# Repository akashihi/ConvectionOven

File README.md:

<!-- Improved compatibility of back to top link: See: https://github.com/othneildrew/Best-README-Template/pull/73 -->

<h3 align="center">Adler Ad 6304 Convection Oven controller board</h3>
<div>
  <p align="center">
    Modern replacement for the Adler Ad 6304 control circuit. 
    <br />
    <a href="https://github.com/akashihi/ConvectionOven"><strong>Explore the docs »</strong></a>
    <br />
    <br />
  </p>
</div>

<!-- TABLE OF CONTENTS -->
<details>
  <summary>Table of Contents</summary>
  <ol>
    <li>
      <a href="#about-the-project">About The Project</a>
    </li>
    <li>
      <a href="#getting-started">Getting Started</a>
      <ul>
        <li><a href="#housing">Housing</a></li>
        <li><a href="#controls">Controls</a></li>
        <li><a href="#hall-sensor">Hall sensor</a></li>
        <li><a href="#pcb">PCB</a></li>
        <li><a href="#firmware">Firmware</a></li>
      </ul>
    </li>
    <li><a href="#usage">Usage</a></li>
    <li><a href="#roadmap">Roadmap</a></li>
    <li><a href="#contributing">Contributing</a></li>
    <li><a href="#license">License</a></li>
    <li><a href="#contact">Contact</a></li>
  </ol>
</details>

<!-- ABOUT THE PROJECT -->
## About The Project

This is a drop-in replacement of an analog control circuit of the Adler Ad 6304 oven.

The updated control circuit provides the following improvements to the original circuit:

* Easily cancellable timer
* Magnetic handle position sensor
* PID temperature control
* LCD user interface
* Overheat protection
* Motor protection (currently disabled in firmware)
* Sleeping mode (currently disabled)

<p align="right">(<a href="#readme-top">back to top</a>)</p>

<!-- GETTING STARTED -->
## Getting Started

Get an Adler Ad 6304 oven that you would like to upgrade. Broken oven is fine too, 
in case heater element and motor are still working. You will need to completely disassemble
the oven and remove most of it. However, some elements will be reused:

* Heater and heater wires
* Motor and motor wires
* Thermistor. It is hidden in the white braid and mounted directly to the upper fan housing. 
Leave it as it is or move closer to the power outlet.

Everything else, including the plastic enclosure, could be thrown to the trash :D 

### Housing

Housing consists of five 3D printable parts:

* Inner and outer axles
* Upper and lower handle parts
* The actual electronics housing

Both axles and handle parts are easy to print. The housing is more tricky, as you need 
supports only for the bigger overhands, like encoders insets or cut for a handle. 
You *do not* need supports for the ventilation cuts. Putting supports there will make your life
much harder, as those supports are almost impossible to remove.

While assembling the housing, you need to put inner axles through the housing and glue them
to the outer axles, so they will become a real axle. For the handle you'll need some M3 bolts
and nuts. Additionally, you need to put several strong 6mmx3mm magnets into the magnet
pocket of the lower handle.

After assembling the handle, put the M3 insets into the hall sensor PCB mounting holes,
screen mounting holes and the main PCB mounting holes.

As the last step, mount the IEC 60320 C14 connector to the respective slot on the housing side.

<p align="right">(<a href="#readme-top">back to top</a>)</p>

### Controls

All controls are mounted to the housing. You will need to mount:

* Two encoders, one for the temperature setting, one for the timer setting
* Two buttons. One for the sleep mode (unused atm), one to switch the cooking mode on and off
* Two LEDs, one shows whether oven is cooking or not, another one shows the heater state
* 16x2 HD44780 screen with 3.3V support. The 5V screens will not work in this design.

<p align="right">(<a href="#readme-top">back to top</a>)</p>

### Hall sensor

Hall sensor is mounted on a separate PCB under the handle. This design uses omni-polar
hall sensor with an open-drain output.

<p align="right">(<a href="#readme-top">back to top</a>)</p>

### PCB

Control PCB is a four layer PCB, split into hot side and cold side. Follow the schematics
and PCB design for the assembly. Additional guidance:

* The U3 IC is required, as it closes the motor control circuit. However, it is not
used in the firmware, so rest of the components (C3, C4, R11, R12, D1, C20) could be omitted for now.
* You can skip the U4 IC and related components (R10, C11, C6, C5)
* You need to short circuit R25, as there is no sleep mode implemented yet
* TRIACs Q1 and Q2 *require* heatsinks
* You may test the cold side of the circuit by injecting power (+5V) directly to the J4

Assembled PCB should be put into the housing and connected to the controls, power socket, heater and
motor. Please connect motor to the control channel equipped with a current sensor. It
is recommended to have a fuse between the power socket and the control PCB. Same way
connect the thermistor, mentioned above, in series with the fuse.

<p align="right">(<a href="#readme-top">back to top</a>)</p>

### Firmware

Precompiled firmware is provided in the `fw.bin` file. 

The firmware is written in Rust and could be compiled with the following commands:

```shell
cargo build --release
cargo objcopy --release --bin fw -- -O binary fw.bin
```

You can upload the firmware with a `st-flash` tool:

```shell
st-flash erase 
st-flash write fw.hex 0x8000000
st-flash reset
```

The oven should start immediately after reset

<p align="right">(<a href="#readme-top">back to top</a>)</p>

## Usage

To start cooking you have to set a timer (up to 3 hours) and desired temperature (up to 250 degrees),
lower the handle and press cooking button. The oven will start immediately.

Raising the handle or pressing the cooking button stops the motor and heater instantly.

You can adjust the timer and desired temperature during the cooking. In one minute before
the timer expiration you will get a short beep accompanied by a longer beep after timer
expiration.

After cooking please immediately open the oven and put a top lid on the lid rack to 
avoid circuit overheat.  

<p align="right">(<a href="#readme-top">back to top</a>)</p>

<!-- ROADMAP -->
## Roadmap

- [ ] Implement sleep mode
- [ ] Implement motor protection

<p align="right">(<a href="#readme-top">back to top</a>)</p>

<!-- CONTRIBUTING -->
## Contributing

Contributions are what make the open source community such an amazing place to learn, inspire, and create. Any contributions you make are **greatly appreciated**.

If you have a suggestion that would make this better, please fork the repo and create a pull request.

1. Fork the Project
2. Create your Feature Branch (`git checkout -b feature/AmazingFeature`)
3. Commit your Changes (`git commit -m 'Add some AmazingFeature'`)
4. Push to the Branch (`git push origin feature/AmazingFeature`)
5. Open a Pull Request

<p align="right">(<a href="#readme-top">back to top</a>)</p>

<!-- LICENSE -->
## License

Distributed under the GPLv3 License. See `LICENSE.txt` for more information.

<p align="right">(<a href="#readme-top">back to top</a>)</p>

<!-- CONTACT -->
## Contact

Denis Chaplygin - @akashihi@mathstodon.xyz - akashihi@gmail.com

Project Link: [https://github.com/akashihi/ConvectionOven](https://github.com/github_username/repo_name)

<p align="right">(<a href="#readme-top">back to top</a>)</p>

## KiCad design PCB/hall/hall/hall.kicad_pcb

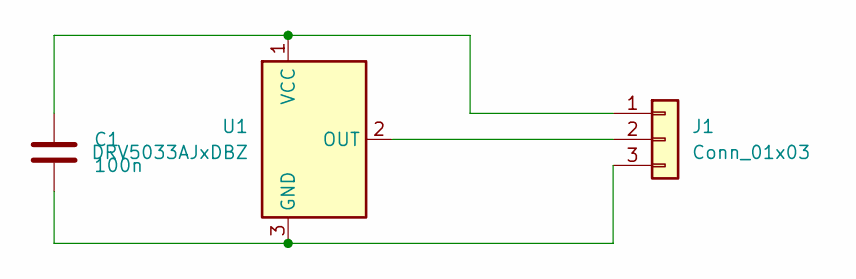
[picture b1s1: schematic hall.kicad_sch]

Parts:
C1: 100n; C_0603_1608Metric
J1: Conn_01x03; PinHeader_1x03_P2.00mm_Vertical
U1: DRV5033AJxDBZ; SOT-23

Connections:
unnamed: C1.1, J1.1, U1.1 (VCC)
unnamed: J1.2, U1.2 (OUT)
unnamed: C1.2, J1.3, U1.3 (GND)

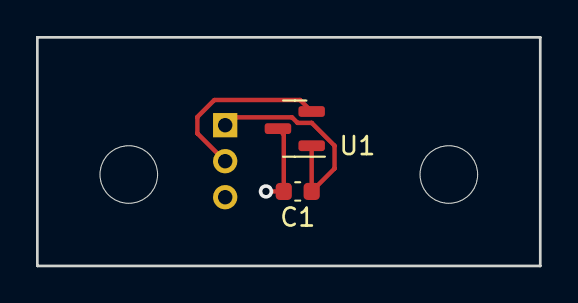
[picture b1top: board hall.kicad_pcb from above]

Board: 2 copper layers, 27.9 x 12.7 mm, 3 parts (1 on the bottom side), 3 nets.

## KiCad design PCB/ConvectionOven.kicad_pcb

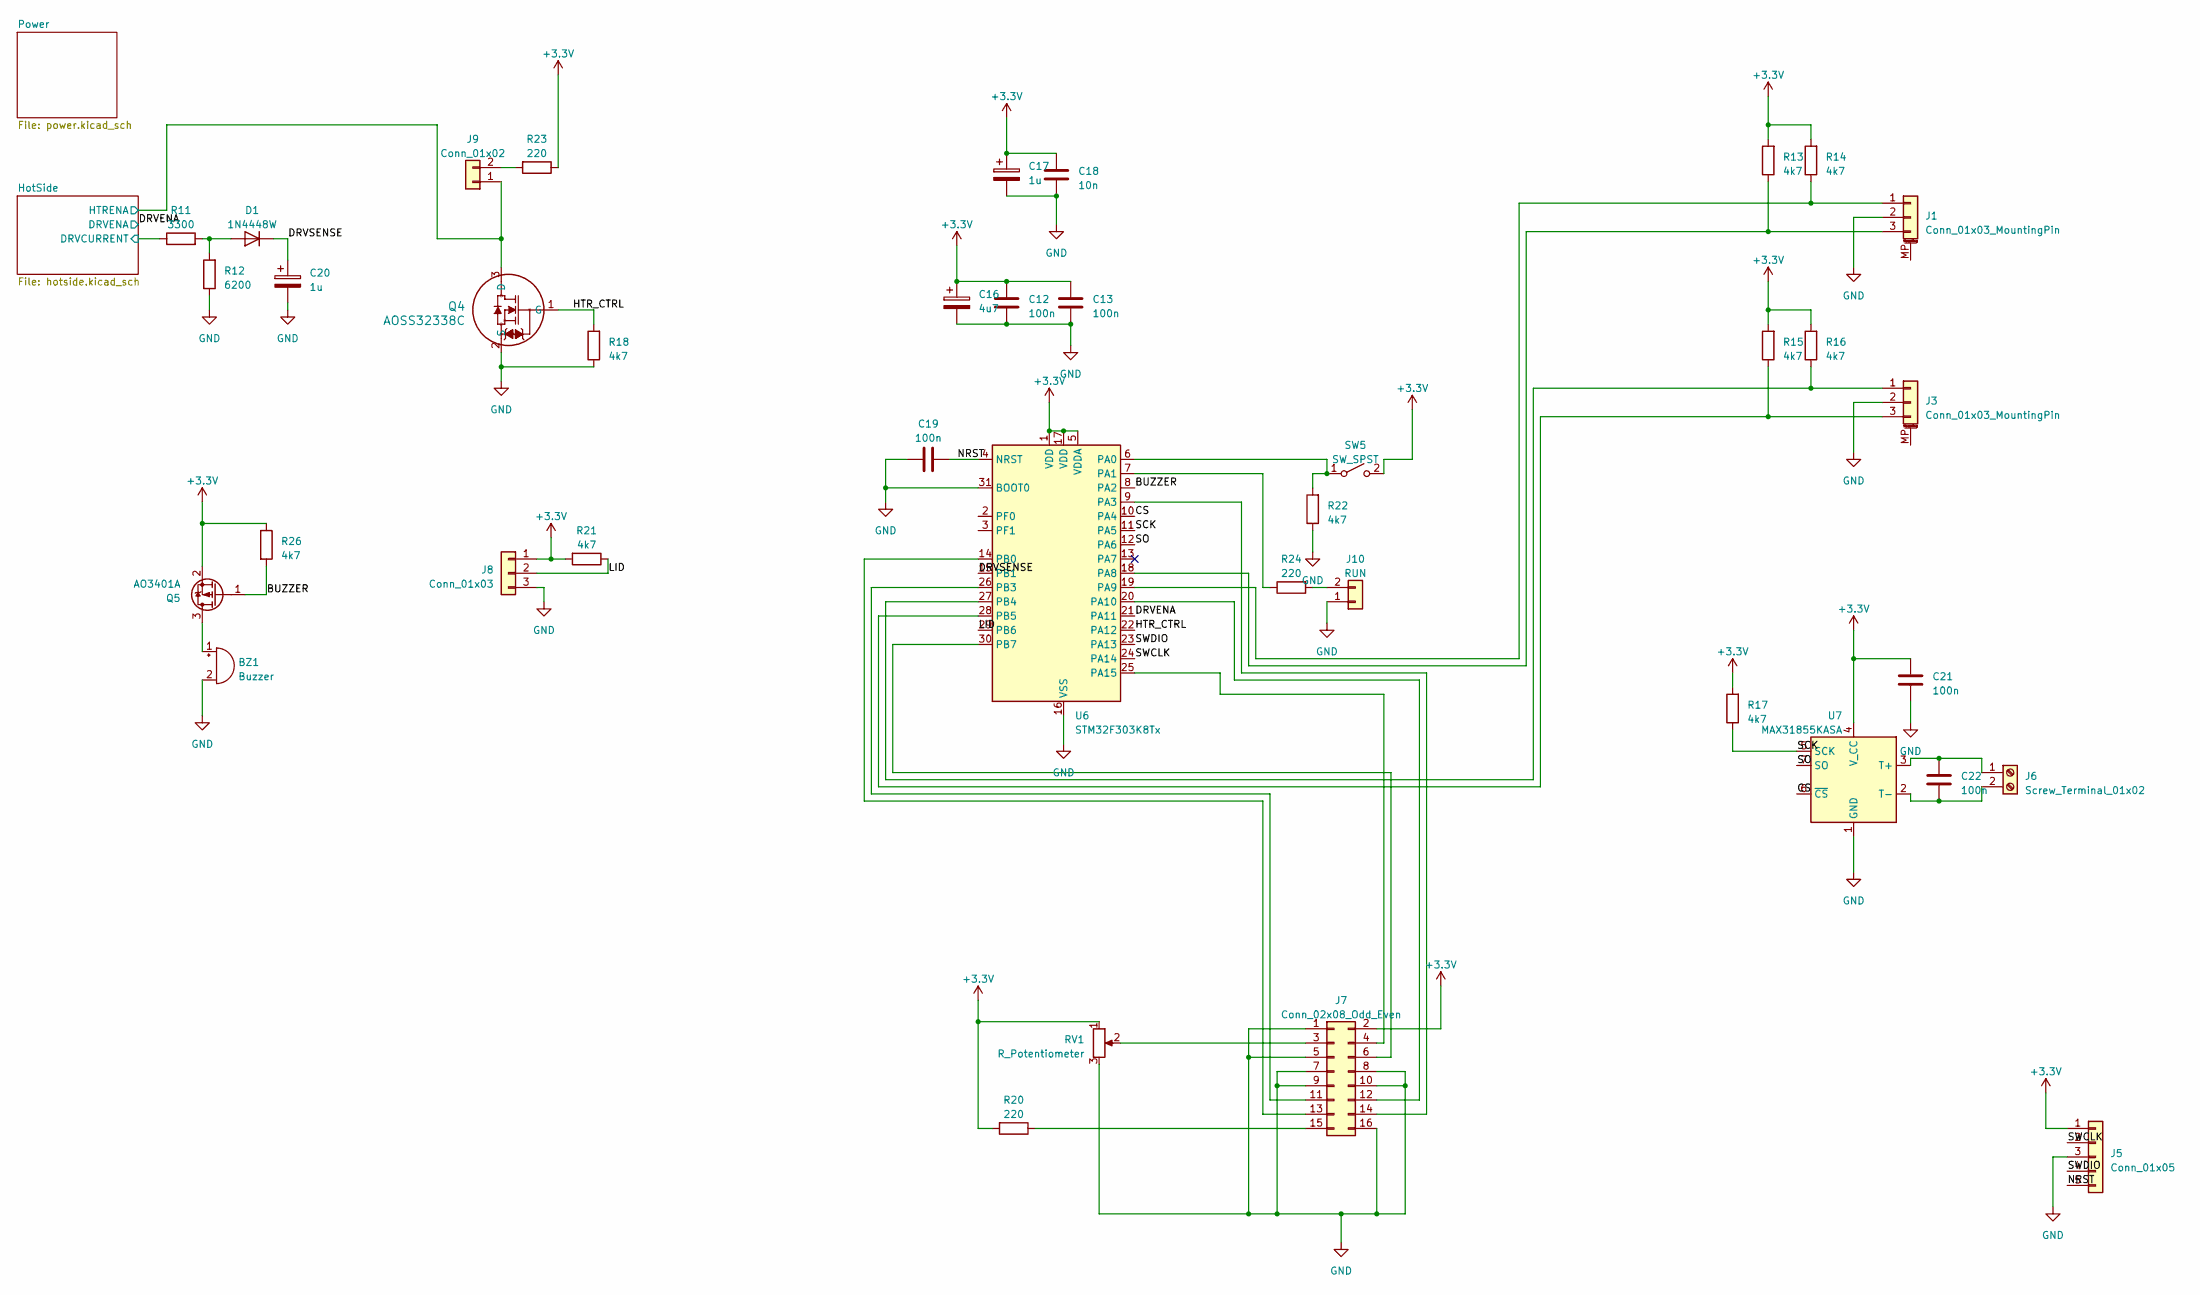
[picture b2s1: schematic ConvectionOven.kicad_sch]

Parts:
BZ1: Buzzer; Buzzer_12x9.5RM7.6
C12, C13, C19, C21, C22: 100n; C_0402_1005Metric_Pad0.74x0.62mm_HandSolder
C16: 4u7; C_Elec_4x5.4
C17, C20: 1u; C_0805_2012Metric_Pad1.18x1.45mm_HandSolder
C18: 10n; C_0805_2012Metric_Pad1.18x1.45mm_HandSolder
D1: 1N4448W; D_SOD-123
J1, J3: Conn_01x03_MountingPin; PinSocket_1x03_P2.00mm_Vertical
J5: Conn_01x05; PinHeader_1x05_P2.54mm_Vertical
J6: Screw_Terminal_01x02; TerminalBlock_Altech_AK300-2_P5.00mm
J7: Conn_02x08_Odd_Even; PinHeader_2x08_P2.54mm_Vertical
J8: Conn_01x03; PinSocket_1x03_P2.00mm_Vertical
J9: Conn_01x02; PinSocket_1x02_P2.00mm_Vertical
J10: RUN; PinSocket_1x02_P2.00mm_Vertical
Q4: AOSS32338C; SOT-23-3
Q5: AO3401A; SOT-23
R11: 3300; R_0805_2012Metric_Pad1.20x1.40mm_HandSolder
R12: 6200; R_1206_3216Metric_Pad1.30x1.75mm_HandSolder
R13, R14, R15, R16, R17, R18, R21, R22, R26: 4k7; R_0805_2012Metric_Pad1.20x1.40mm_HandSolder
R20, R23, R24: 220; R_0805_2012Metric_Pad1.20x1.40mm_HandSolder
RV1: R_Potentiometer; Potentiometer_Bourns_3296W_Vertical
SW5: SW_SPST; PinSocket_1x02_P2.00mm_Vertical
U6: STM32F303K8Tx; LQFP-32_7x7mm_P0.8mm
U7: MAX31855KASA; SOIC-8_3.9x4.9mm_P1.27mm

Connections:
+3.3V: C12.1, C13.1, C16.1, C17.1, C18.1, C21.1, J5.1, J7.2, J8.1, Q5.2 (S), R13.2, R14.2, R15.2, R16.2, R17.2, R20.2, R21.2, R23.1, R26.1, RV1.1, SW5.2 (B), U6.1 (VDD), U6.5 (VDDA), U6.17 (VDD), U7.4 (V_CC); also elsewhere on the board
/BUZZER: Q5.1 (G), R26.2, U6.8 (PA2)
/CS: U6.10 (PA4), U7.6 (~CS)
/DRVENA: U6.21 (PA11); also elsewhere on the board
/DRVSENSE: C20.1, D1.1 (K), U6.15 (PB1)
/HTR_CTRL: Q4.1 (G), R18.2, U6.22 (PA12)
/HotSide/DRVCURRENT: R11.1; also elsewhere on the board
/HotSide/HTRENA: J9.1, Q4.3 (D); also elsewhere on the board
/LID: J8.2, R21.1, U6.29 (PB6)
/NRST: C19.2, J5.5, U6.4 (NRST)
/SCK: R17.1, U6.11 (PA5), U7.5 (SCK)
/SO: U6.12 (PA6), U7.7 (SO)
/SWCLK: J5.2, U6.24 (PA14)
/SWDIO: J5.4, U6.23 (PA13)
GND: BZ1.2 (+), C12.2, C13.2, C16.2, C17.2, C18.2, C19.1, C20.2, C21.2, J1.2, J3.2, J5.3, J7.1, J7.5, J7.7, J7.8, J7.9, J7.10, J7.16, J8.3, J10.1, Q4.2 (S), R12.1, R18.1, R22.1, RV1.3, U6.16 (VSS), U6.31 (BOOT0), U6.32 (VSS), U7.1 (GND); also elsewhere on the board
unnamed: BZ1.1 (-), Q5.3 (D)
unnamed: D1.2 (A), R11.2, R12.2
unnamed: J1.1, R14.1, U6.19 (PA9)
unnamed: J1.3, R13.1, U6.18 (PA8)
unnamed: J3.1, R16.1, U6.27 (PB4)
unnamed: J3.3, R15.1, U6.28 (PB5)
unnamed: C22.1, J6.1, U7.3 (T+)
unnamed: C22.2, J6.2, U7.2 (T-)
unnamed: J7.3, RV1.2
unnamed: J7.4, U6.25 (PA15)
unnamed: J7.6, U6.30 (PB7)
unnamed: J7.11, U6.26 (PB3)
unnamed: J7.12, U6.20 (PA10)
unnamed: J7.13, U6.14 (PB0)
unnamed: J7.14, U6.9 (PA3)
unnamed: J7.15, R20.1
unnamed: J9.2, R23.2
unnamed: J10.2, R24.2
unnamed: R22.2, SW5.1 (A), U6.6 (PA0)
unnamed: R24.1, U6.7 (PA1)

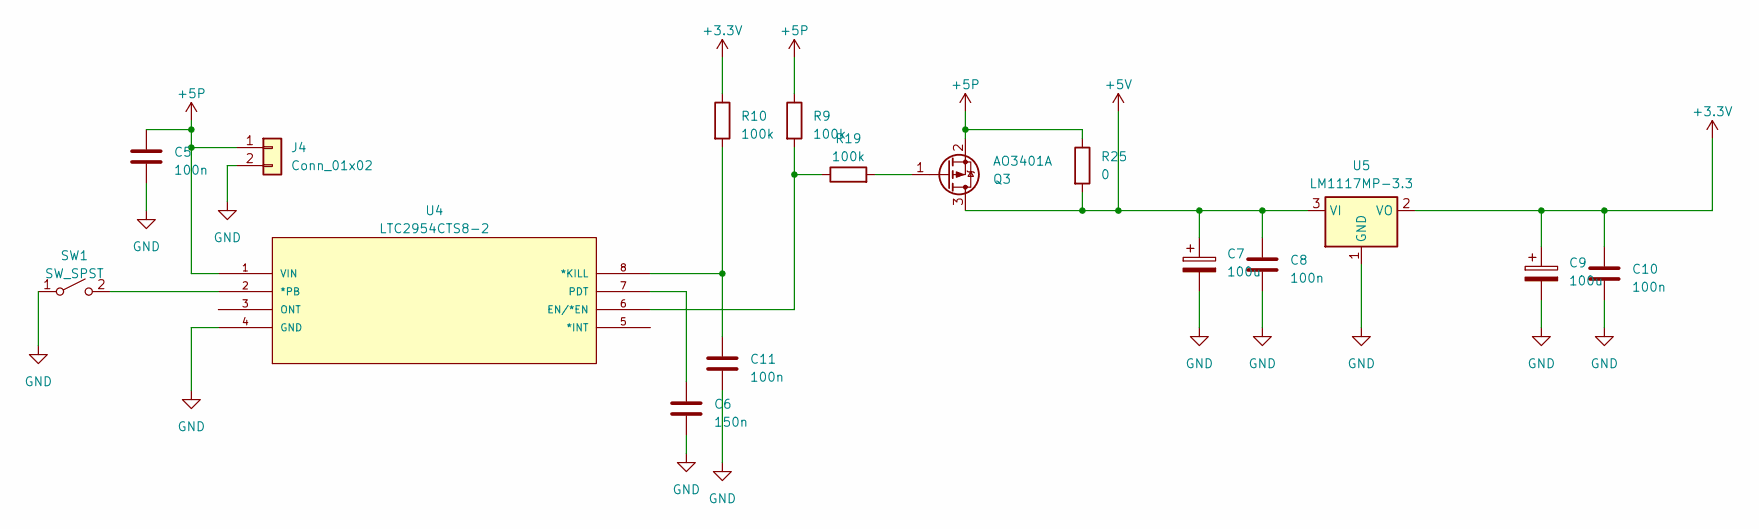
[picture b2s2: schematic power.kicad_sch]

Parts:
C5, C8, C10, C11: 100n; C_0402_1005Metric_Pad0.74x0.62mm_HandSolder
C6: 150n; C_0402_1005Metric_Pad0.74x0.62mm_HandSolder
C7, C9: 100u; CP_EIA-7343-15_Kemet-W_Pad2.25x2.55mm_HandSolder
J4: Conn_01x02; PinHeader_1x02_P2.54mm_Vertical
Q3: AO3401A; SOT-23
R9, R19: 100k; R_0805_2012Metric_Pad1.20x1.40mm_HandSolder
R10: 100k; R_0603_1608Metric_Pad0.98x0.95mm_HandSolder
R25: 0; R_0805_2012Metric_Pad1.20x1.40mm_HandSolder
SW1: SW_SPST; PinSocket_1x02_P2.00mm_Vertical
U4: LTC2954CTS8-2; TSOT-23-8_HandSoldering; MANUFACTURER_PART_NUMBER ltc2954cts82
U5: LM1117MP-3.3; SOT-223-3_TabPin2

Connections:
+3.3V: C9.1, C10.1, R10.1, U5.2 (VO); also elsewhere on the board
+5P: C5.1, J4.1, Q3.2 (S), R9.1, R25.1, U4.1 (VIN); also elsewhere on the board
+5V: C7.1, C8.1, Q3.3 (D), R25.2, U5.3 (VI); also elsewhere on the board
GND: C5.2, C6.2, C7.2, C8.2, C9.2, C10.2, C11.2, J4.2, SW1.1 (A), U4.4 (GND), U5.1 (GND); also elsewhere on the board
unnamed: Q3.1 (G), R19.2
unnamed: SW1.2 (B), U4.2 (*PB)
unnamed: C11.1, R10.2, U4.8 (*KILL)
unnamed: R9.2, R19.1, U4.6 (EN/*EN)
unnamed: C6.1, U4.7 (PDT)

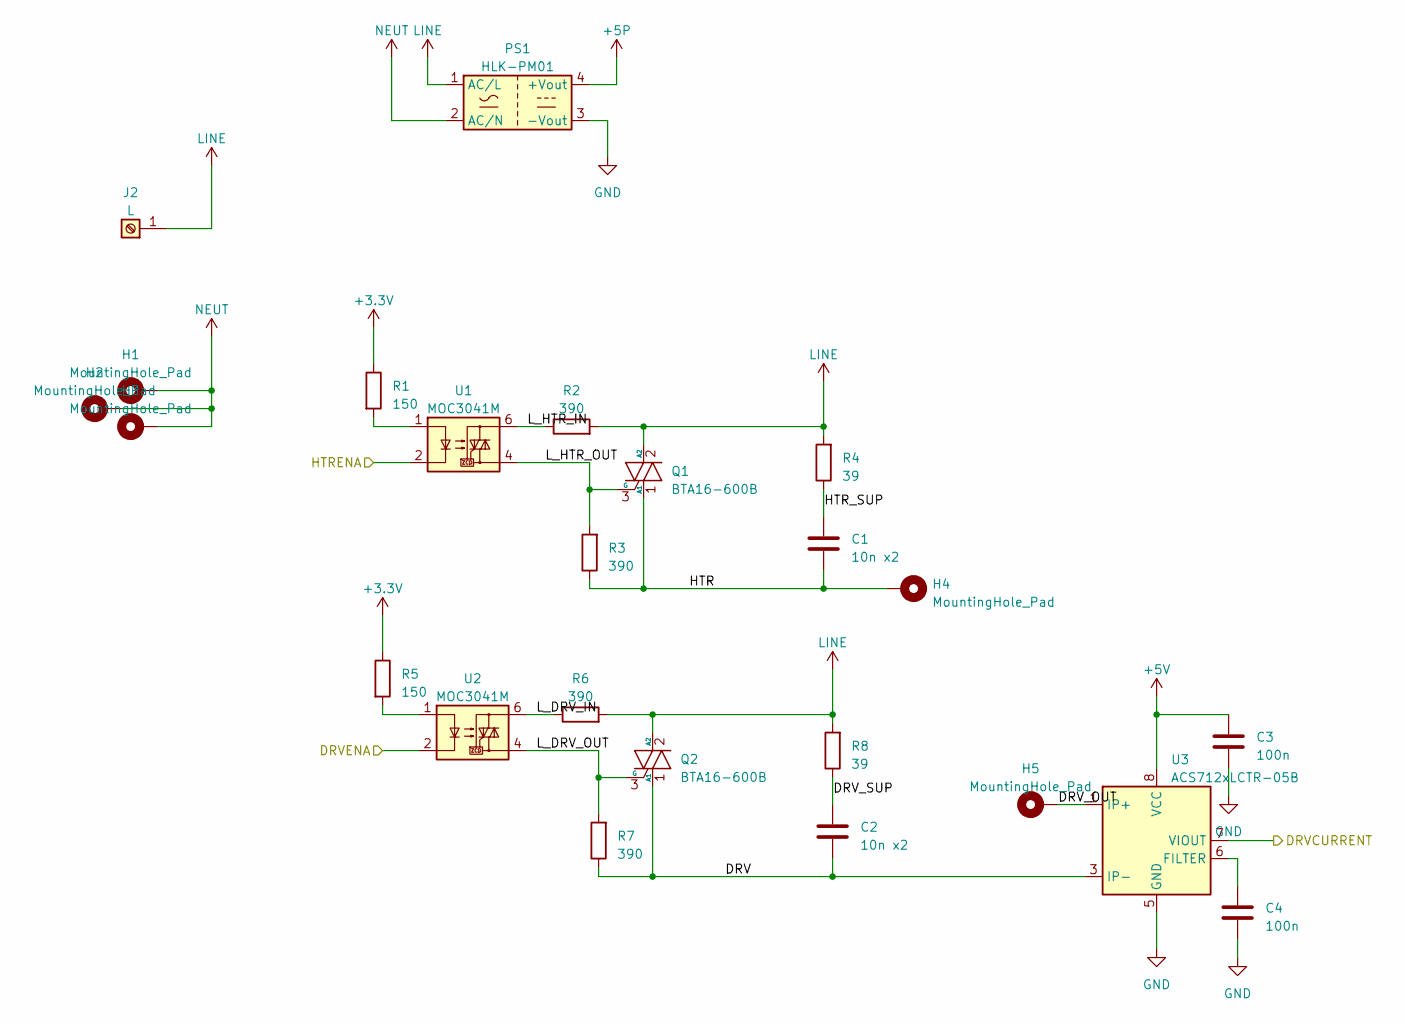
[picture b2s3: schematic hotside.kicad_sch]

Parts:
C1, C2: 10n x2; C_Rect_L16.5mm_W4.7mm_P15.00mm_MKT
C3, C4: 100n; C_0402_1005Metric_Pad0.74x0.62mm_HandSolder
H1, H2, H3, H4, H5: MountingHole_Pad; MountingHole_3.2mm_M3_DIN965_Pad_TopBottom
J2: L; MountingHole_3.2mm_M3_DIN965_Pad_TopBottom
PS1: HLK-PM01; Converter_ACDC_HiLink_HLK-PMxx
Q1, Q2: BTA16-600B; TO-220-3_Vertical
R1, R5: 150; R_0603_1608Metric_Pad0.98x0.95mm_HandSolder
R2, R3, R6, R7: 390; R_Axial_DIN0309_L9.0mm_D3.2mm_P5.08mm_Vertical
R4, R8: 39; R_Axial_DIN0411_L9.9mm_D3.6mm_P7.62mm_Vertical
U1, U2: MOC3041M; DIP-6_W7.62mm
U3: ACS712xLCTR-05B; SOIC-8_3.9x4.9mm_P1.27mm

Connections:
+3.3V: R1.1, R5.1; also elsewhere on the board
+5P: PS1.4 (+Vout); also elsewhere on the board
+5V: C3.1, U3.8 (VCC); also elsewhere on the board
/DRVENA: U2.2; also elsewhere on the board
/HotSide/DRV: C2.2, Q2.1 (A1), R7.1, U3.3 (IP-), U3.4 (IP-)
/HotSide/DRVCURRENT: U3.7 (VIOUT); also elsewhere on the board
/HotSide/DRV_OUT: H5.1, U3.1 (IP+), U3.2 (IP+)
/HotSide/DRV_SUP: C2.1, R8.1
/HotSide/HTR: C1.2, H4.1, Q1.1 (A1), R3.1
/HotSide/HTRENA: U1.2; also elsewhere on the board
/HotSide/HTR_SUP: C1.1, R4.1
/HotSide/L_DRV_IN: R6.1, U2.6
/HotSide/L_DRV_OUT: Q2.3 (G), R7.2, U2.4
/HotSide/L_HTR_IN: R2.1, U1.6
/HotSide/L_HTR_OUT: Q1.3 (G), R3.2, U1.4
GND: C3.2, C4.2, PS1.3 (-Vout), U3.5 (GND); also elsewhere on the board
LINE: J2.1, PS1.1 (AC/L), Q1.2 (A2), Q2.2 (A2), R2.2, R4.2, R6.2, R8.2
NEUT: H1.1, H2.1, H3.1, PS1.2 (AC/N)
unnamed: R1.2, U1.1
unnamed: R5.2, U2.1
unnamed: C4.1, U3.6 (FILTER)

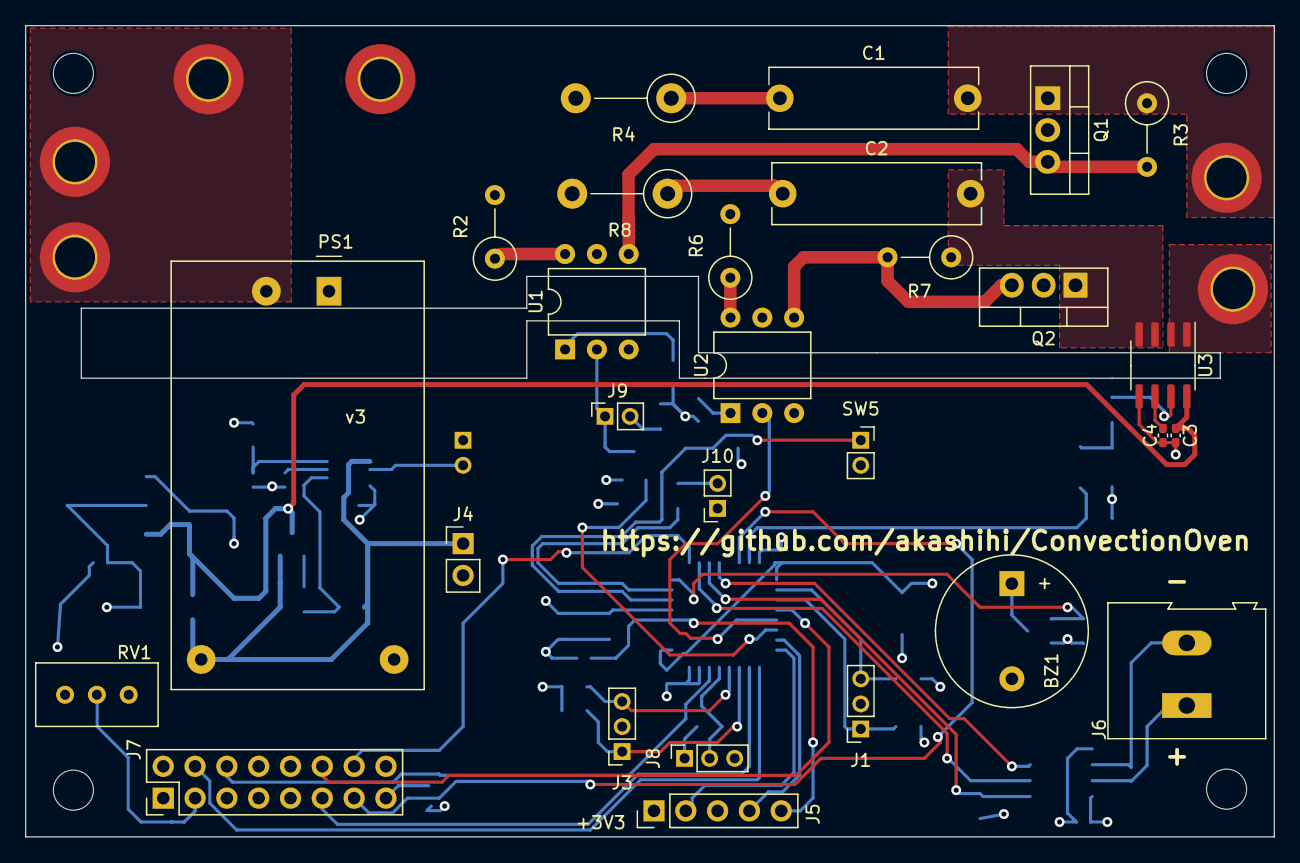
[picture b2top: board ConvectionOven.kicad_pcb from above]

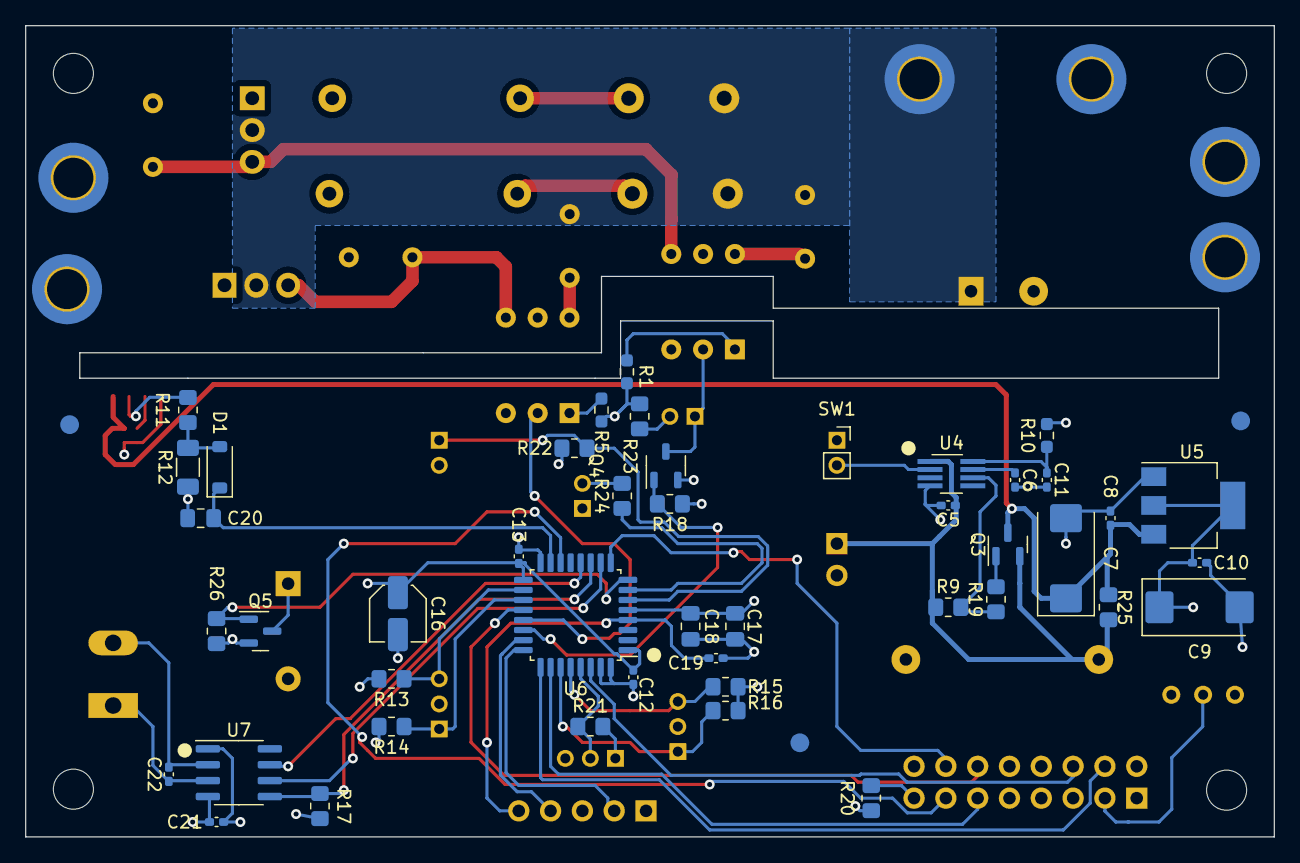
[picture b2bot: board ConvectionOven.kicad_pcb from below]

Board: 4 copper layers, 99.7 x 64.8 mm, 79 parts (45 on the bottom side), 56 nets.

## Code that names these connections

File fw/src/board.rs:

use hd44780_driver::bus::FourBitBus;
use hd44780_driver::{Cursor, HD44780};
use stm32f3xx_hal::gpio::{Alternate, Analog, GpioExt, Input, OpenDrain, Output, PA0, PA1, PA10, PA11, PA12, PA15, PA2, PA3, PA4, PA5, PA6, PA7, PA8, PA9, PB0, PB1, PB3, PB4, PB5, PB6, PB7, PushPull};
use stm32f3xx_hal::hal::blocking::delay::{DelayMs, DelayUs};
use stm32f3xx_hal::pac::{GPIOA, GPIOB, SPI1};
use stm32f3xx_hal::rcc::{AHB, APB2, Clocks};
use stm32f3xx_hal::spi::Spi;
use stm32f3xx_hal::prelude::*;

pub type CookBtn = PA0<Input>;
pub type Lid = PB6<Input>;
pub type CookLd = PA1<Output<PushPull>>;
pub type Buzzer = PA2<Output<OpenDrain>>;
pub type TempEncA = PA8<Alternate<OpenDrain, 6>>;
pub type TempEncB = PA9<Alternate<OpenDrain, 6>>;
pub type TimeEncA = PB4<Alternate<OpenDrain, 2>>;
pub type TimeEncB = PB5<Alternate<OpenDrain, 2>>;
pub type Current = PB1<Analog>;
pub type TcCs = PA4<Output<PushPull>>;
pub type TcSck = PA5<Alternate<PushPull, 5>>;
pub type TcSo = PA6<Alternate<PushPull, 5>>;
pub type TcSi = PA7<Alternate<PushPull, 5>>;
pub type MotorEnable = PA11<Output<OpenDrain>>;
pub type HeaterEnable = PA12<Output<PushPull>>;

pub type SpiBus = Spi<SPI1, (TcSck, TcSo, TcSi), u8>;

type Hd4BitBus = FourBitBus<
    PA15<Output<PushPull>>,
    PB7<Output<PushPull>>,
    PB3<Output<PushPull>>,
    PA10<Output<PushPull>>,
    PB0<Output<PushPull>>,
    PA3<Output<PushPull>>
>;

pub type LCD = HD44780<Hd4BitBus>;

pub struct Board {
    pub cook_btn: CookBtn,
    pub lid: Lid,
    pub cook_ld: CookLd,
    pub buzzer: Buzzer,
    pub temp_encoder: (TempEncA, TempEncB),
    pub time_encoder: (TimeEncA, TimeEncB),
    pub current: Current,
    pub lcd: LCD,
    pub tc_cs: TcCs,
    pub tc_spi: SpiBus,
    pub heater: HeaterEnable,
    pub motor: MotorEnable,
}

impl Board {
    pub fn new<D: DelayUs<u16> + DelayMs<u8>>(gpioa: GPIOA, gpiob: GPIOB, spi: SPI1, ahb: &mut AHB, apb2: &mut APB2, clocks: Clocks, delay: &mut D) -> Self {
        let mut port_a = gpioa.split(ahb);
        let mut port_b = gpiob.split(ahb);

        let cook_btn = port_a.pa0.into_floating_input(&mut port_a.moder, &mut port_a.pupdr);
        let lid = port_b.pb6.into_floating_input(&mut port_b.moder, &mut port_b.pupdr);
        let cook_ld = port_a.pa1.into_push_pull_output(&mut port_a.moder, &mut port_a.otyper);
        let mut buzzer = port_a.pa2.into_open_drain_output(&mut port_a.moder, &mut port_a.otyper);
        buzzer.set_high().unwrap_or_default(); //Speaker output is inverted, so high is the default state

        let temp_enc_a = port_a.pa8.into_af_open_drain::<6>(&mut port_a.moder, &mut port_a.otyper, &mut port_a.afrh);
        let temp_enc_b = port_a.pa9.into_af_open_drain::<6>(&mut port_a.moder, &mut port_a.otyper, &mut port_a.afrh);
        let time_enc_a = port_b.pb4.into_af_open_drain::<2>(&mut port_b.moder, &mut port_b.otyper, &mut port_b.afrl);
        let time_enc_b = port_b.pb5.into_af_open_drain::<2>(&mut port_b.moder, &mut port_b.otyper, &mut port_b.afrl);

        let current = port_b.pb1.into_analog(&mut port_b.moder, &mut port_b.pupdr);

        let mut heater = port_a.pa12.into_push_pull_output(&mut port_a.moder, &mut port_a.otyper);
        heater.set_low().unwrap_or_default();
        let mut motor = port_a.pa11.into_open_drain_output(&mut port_a.moder, &mut port_a.otyper);
        motor.set_high().unwrap_or_default();

        let lcd_rs = port_a.pa15.into_push_pull_output(&mut port_a.moder, &mut port_a.otyper);
        let lcd_e = port_b.pb7.into_push_pull_output(&mut port_b.moder, &mut port_b.otyper);
        let lcd_d5 = port_b.pb3.into_push_pull_output(&mut port_b.moder, &mut port_b.otyper);
        let lcd_d6 = port_a.pa10.into_push_pull_output(&mut port_a.moder, &mut port_a.otyper);
        let lcd_d7 = port_b.pb0.into_push_pull_output(&mut port_b.moder, &mut port_b.otyper);
        let lcd_d8 = port_a.pa3.into_push_pull_output(&mut port_a.moder, &mut port_a.otyper);

        let lcd = HD44780::new_4bit(lcd_rs, lcd_e, lcd_d5, lcd_d6, lcd_d7, lcd_d8, delay)
            .and_then(|mut l| {
                l.reset(delay)?;
                Result::Ok(l)
            })
            .and_then(|mut l| {
                l.clear(delay)?;
                Result::Ok(l)
            })
            .and_then(|mut l| {
                l.set_cursor_visibility(Cursor::Invisible, delay)?;
                Result::Ok(l)
            })
            .unwrap();

        let tc_cs = port_a.pa4.into_push_pull_output(&mut port_a.moder, &mut port_a.otyper);
        let tc_sck = port_a.pa5.into_af_push_pull::<5>(&mut port_a.moder, &mut port_a.otyper, &mut port_a.afrl);
        let tc_so = port_a.pa6.into_af_push_pull::<5>(&mut port_a.moder, &mut port_a.otyper, &mut port_a.afrl);
        let tc_si = port_a.pa7.into_af_push_pull::<5>(&mut port_a.moder, &mut port_a.otyper, &mut port_a.afrl);

        let tc_spi: SpiBus = Spi::new(spi, (tc_sck, tc_so, tc_si), 100.kHz(), clocks, apb2);

        Board { cook_btn, lid, cook_ld, buzzer, temp_encoder: (temp_enc_a, temp_enc_b), time_encoder: (time_enc_a, time_enc_b), current, lcd, tc_cs, tc_spi, heater, motor }
    }
}

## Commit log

2024-05-22 Public release
2024-05-22 Image fixed
